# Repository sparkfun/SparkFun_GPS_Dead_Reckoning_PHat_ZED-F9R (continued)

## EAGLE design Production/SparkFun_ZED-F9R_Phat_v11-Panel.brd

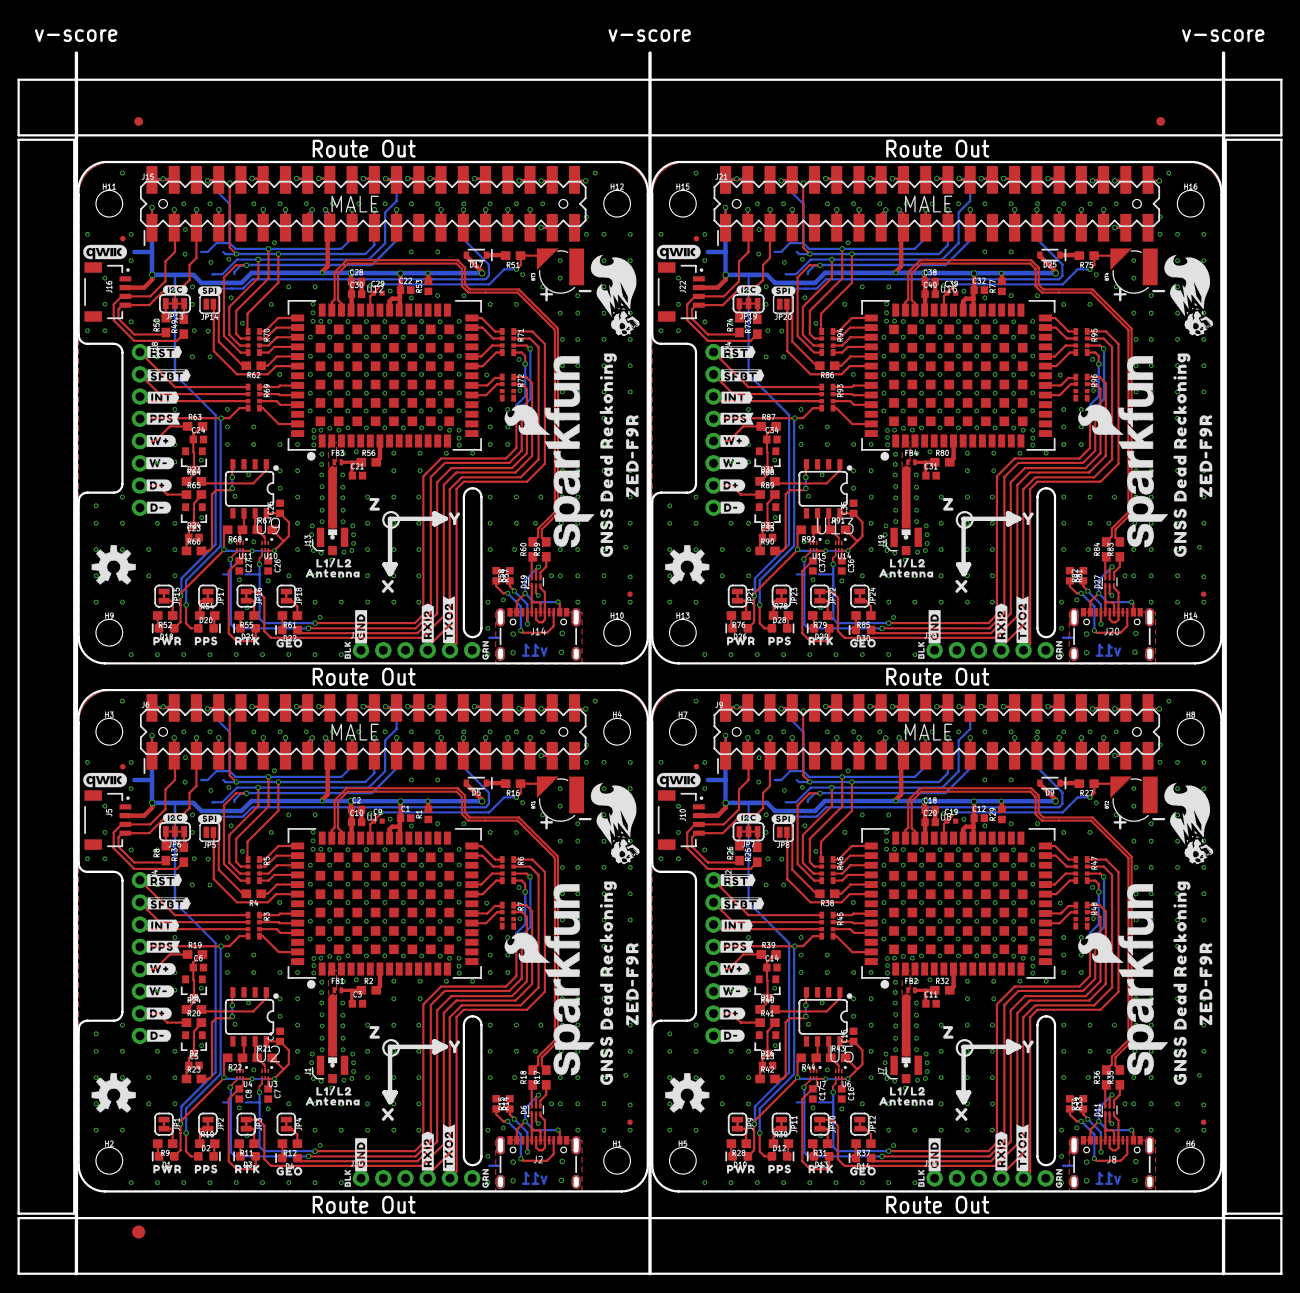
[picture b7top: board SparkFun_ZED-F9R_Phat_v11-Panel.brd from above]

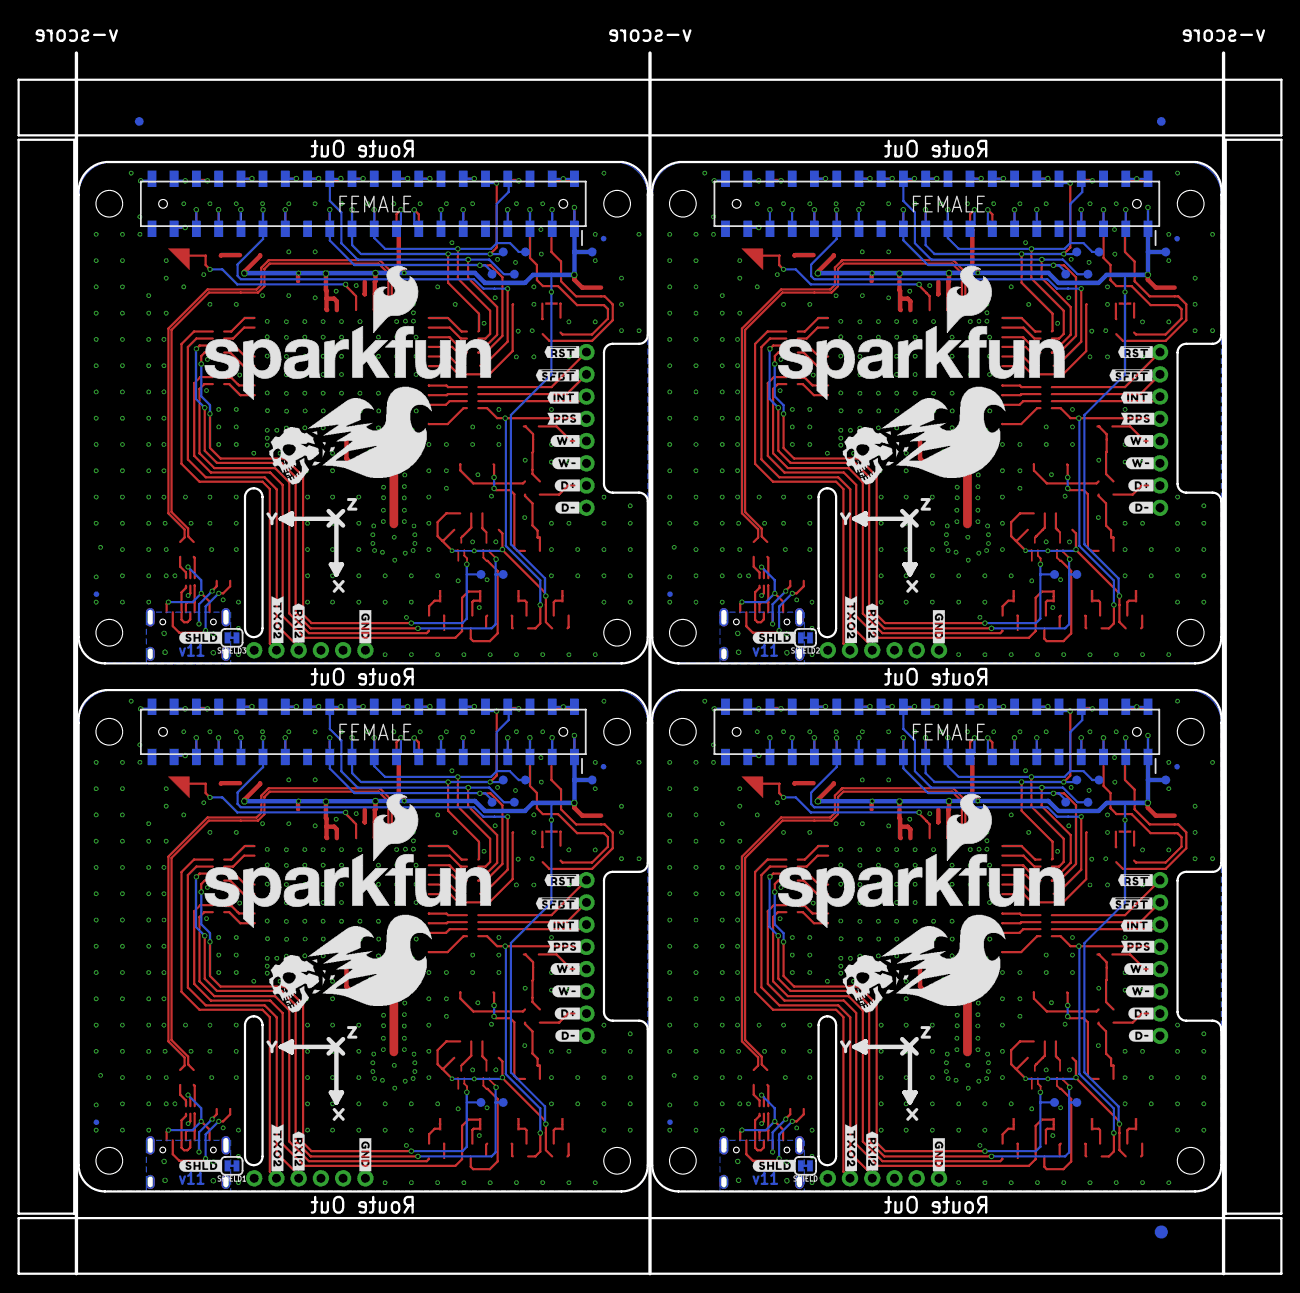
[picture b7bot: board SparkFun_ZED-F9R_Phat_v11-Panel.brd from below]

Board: 2 copper layers, 144.2 x 139.4 mm, 498 parts (111 on the bottom side), 352 nets.

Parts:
BT1, BT2, BT3, BT4: RELOWABLE_BATTERY_MS421R; MS421R_IV03E
C1, C2, C10, C12, C18, C20, C22, C28, C30, C32, C38, C40: 1.0uF; 0402
C3, C11, C21, C31: 47pF; 0402
C4, C7, C8, C15, C16, C17, C25, C26, C27, C35, C36, C37: 0.1uF; 0402
C5, C6, C13, C14, C23, C24, C33, C34: 1nF; 0402
C9, C19, C29, C39: 2.2uF; 0402-TIGHT
D1, D10, D18, D26: RED; LED-0603
D2, D3, D4, D12, D13, D14, D20, D21, D22, D28, D29, D30: BLUE; LED-0603
D5, D9, D17, D25: 0.5A/40V/420mV; SOD-323
D6, D11, D19, D27: PRTR5V0U2F; SOT886
D7, D8, D15, D16, D23, D24, D31, D32: 15V; SOT23-3
E$1, E$2, E$3, E$4: FIDUCIAL-1X2
E$5, E$6: FIDUCIAL-1.5X3
FB1, FB2, FB3, FB4: 120NH; 0402_MURATA
FD1, FD2, FD3, FD4, FD5, FD6, FD7, FD8, FD9, FD10, FD11, FD12, FD13, FD14, FD15, FD16: FIDUCIALUFIDUCIAL; FIDUCIAL-MICRO
H1, H2, H3, H4, H5, H6, H7, H8, H9, H10, H11, H12, H13, H14, H15, H16: STAND-OFFTIGHT; STAND-OFF-TIGHT
J1, J7, J13, J19: U.FL
J2, J8, J14, J20: USB-C-16P-2LAYER-PADS
J3, J11, J17, J23: 1X06_NO_SILK
J4, J12, J18, J24: 1X08_NO_SILK
J5, J10, J16, J22: QWIIC_RIGHT_ANGLE; JST04_1MM_RA
J6, J9, J15, J21: RASPBERRYPI-40-PIN-GPIO_SMD_STACK_NOHOLES_NOREF; RASPBERRY_PI_HAT_40_PIN_SMD_STACKABLE_NOHOLES_NOREF
JP1, JP2, JP3, JP4, JP9, JP10, JP11, JP12, JP15, JP16, JP17, JP18, JP21, JP22, JP23, JP24: JUMPER-SMT_2_NC_TRACE_SILK; SMT-JUMPER_2_NC_TRACE_SILK
JP5, JP8, JP14, JP20: JUMPER-SMT_2_NO_SILK; SMT-JUMPER_2_NO_SILK
JP6, JP7, JP13, JP19: JUMPER-SMT_3_2-NC_TRACE_SILK; SMT-JUMPER_3_2-NC_TRACE_SILK
LOGO1, LOGO6, LOGO9, LOGO12: QWIIC_LOGO_5MM; QWIIC_5MM
LOGO2, LOGO5, LOGO8, LOGO11: OSHW-LOGOM; OSHW-LOGO-M
LOGO3, LOGO4, LOGO7, LOGO10: SFE_LOGO_NAME_FLAME.2_INCH; SFE_LOGO_NAME_FLAME_.2
R1, R29, R53, R77: 100K; 0402
R2, R4, R32, R38, R56, R62, R80, R86: 33; 0603
R3, R5, R6, R7, R45, R46, R47, R48, R69, R70, R71, R72, R93, R94, R95, R96: 33; 1206_RA
R8, R10, R11, R12, R13, R25, R26, R30, R31, R37, R49, R50, R54, R55, R61, R73, R74, R78, R79, R85: 2.2k; 0603
R9, R28, R52, R76: 1k; 0603
R14, R15, R33, R34, R57, R58, R81, R82: 5.1k; 0402
R16, R19, R20, R27, R39, R41, R51, R63, R65, R75, R87, R89: 3.3k; 0603
R17, R18, R35, R36, R59, R60, R83, R84: 27; 0603
R21, R22, R43, R44, R67, R68, R91, R92: 910; 0603
R23, R24, R40, R42, R64, R66, R88, R90: 470; 0603
SHIELD, SHIELD1, SHIELD2, SHIELD3: JUMPER-SMT_2_NC_TRACE_SILK; SMT-JUMPER_2_NC_TRACE_SILK
TP1, TP2, TP3, TP4, TP5, TP6, TP7, TP8, TP9, TP10, TP11, TP12, TP13, TP14, TP15, TP16, TP17, TP18, TP19, TP20, TP21, TP22, TP23, TP24, TP25, TP26, TP27, TP28: TEST-POINT3X4; PAD.03X.04
U1, U8, U12, U16: U-BLOX_ZED-F9R; UBLOX_ZED_F9R
U2, U5, U9, U13: DUAL-OPTO_HCPL-073LSOIC-8; SO08
U3, U4, U6, U7, U10, U11, U14, U15: UHS_INVERTER_SCHMITT_TRIGGER_MPAK2; SIP6_MICROPAK2
U$1, U$48, U$92, U$136: ##RST##28
U$2, U$49, U$93, U$137: ##SFBT##30
U$3, U$59, U$103, U$147: PPS9
U$4, U$58, U$102, U$146: PWR7
U$5, U$61, U$105, U$149: GEO11
U$6, U$66, U$110, U$154: #RXI2#34
U$7, U$50, U$94, U$138: #INT#1
U$8, U$51, U$95, U$139: #PPS#3
U$9, U$30, U$89, U$133: SFE_LOGO_NAME_FLAME_.3@1
U$10, U$67, U$111, U$155: #TXO2#235
U$11, U$52, U$96, U$140: #W##2253
U$12, U$53, U$97, U$141: #W##2254
U$13, U$54, U$98, U$142: #D##2249
U$14, U$77, U$121, U$165: GNSS_DEAD_RECKONING25
U$15, U$55, U$99, U$143: #D##2250
U$16, U$68, U$112, U$156: ZED#F9R25
U$17, U$62, U$106, U$150: BLK22
U$18, U$19, U$64, U$65, U$108, U$109, U$152, U$153: #GND#20
U$20, U$56, U$100, U$144: #SPI#4
U$21, U$78, U$122, U$166: L1#L26
U$22, U$57, U$101, U$145: #I2C#5
U$23, U$60, U$104, U$148: RTK13
U$24, U$63, U$107, U$151: GRN23
U$25, U$28, U$85, U$86, U$129, U$130, U$173, U$174: Z20
U$26, U$29, U$87, U$88, U$131, U$132, U$175, U$176: Y19
U$27, U$45, U$83, U$84, U$127, U$128, U$171, U$172: X18
U$31, U$36, U$46, U$47, U$90, U$91, U$134, U$135: DEAD#RECKONING#GPS#BOARD#SILK#FINAL#JPG
U$32, U$69, U$113, U$157: ##RST##27
U$33, U$70, U$114, U$158: ##SFBT##29
U$34, U$71, U$115, U$159: #INT#0
U$35, U$72, U$116, U$160: #PPS#2
U$37, U$73, U$117, U$161: #W##2251
U$38, U$74, U$118, U$162: #W##2252
U$39, U$75, U$119, U$163: #D##2247
U$40, U$76, U$120, U$164: #D##2248
U$41, U$79, U$123, U$167: ANTENNA6
U$42, U$80, U$124, U$168: #TXO2#236
U$43, U$81, U$125, U$169: #RXI2#35
U$44, U$82, U$126, U$170: #SHLD#2258

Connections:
3.3V: C1.1, C2.1, C4.1, C7.1, C8.1, C10.1, D1.A, D3.A, D5.A, J5.2, J6.1, J6.1B, J6.17, J6.17B, JP6.2, R1.2, R21.2, R22.2, TP5.P$1, U1.P33, U1.P34, U1.P38, U2.8, U3.P6, U4.P6
3.3V1: C12.1, C15.1, C16.1, C17.1, C18.1, C20.1, D9.A, D10.A, D13.A, J9.1, J9.1B, J9.17, J9.17B, J10.2, JP7.2, R29.2, R43.2, R44.2, TP12.P$1, U5.8, U6.P6, U7.P6, U8.P33, U8.P34, U8.P38
3.3V2: C22.1, C25.1, C26.1, C27.1, C28.1, C30.1, D17.A, D18.A, D21.A, J15.1, J15.1B, J15.17, J15.17B, J16.2, JP13.2, R53.2, R67.2, R68.2, TP19.P$1, U9.8, U10.P6, U11.P6, U12.P33, U12.P34, U12.P38
3.3V3: C32.1, C35.1, C36.1, C37.1, C38.1, C40.1, D25.A, D26.A, D29.A, J21.1, J21.1B, J21.17, J21.17B, J22.2, JP19.2, R77.2, R91.2, R92.2, TP26.P$1, U13.8, U14.P6, U15.P6, U16.P33, U16.P34, U16.P38
5V: J6.2, J6.2B, J6.4, J6.4B
5V1: J9.2, J9.2B, J9.4, J9.4B
5V2: J15.2, J15.2B, J15.4, J15.4B
5V3: J21.2, J21.2B, J21.4, J21.4B
!RESET: J4.1, R3.P1
!RESET1: J12.1, R45.P1
!RESET2: J18.1, R69.P1
!RESET3: J24.1, R93.P1
!SAFEBOOT: J4.2, R3.P2
!SAFEBOOT1: J12.2, R45.P2
!SAFEBOOT2: J18.2, R69.P2
!SAFEBOOT3: J24.2, R93.P2
CE1: J6.26, J6.26B
CE2: J9.26, J9.26B
CE3: J15.26, J15.26B
CE4: J21.26, J21.26B
DIR+: J4.7, R20.1
DIR+1: J12.7, R41.1
DIR+2: J18.7, R65.1
DIR+3: J24.7, R89.1
DIR_IN: R23.2, U2.4
DIR_IN1: R42.2, U5.4
DIR_IN2: R66.2, U9.4
DIR_IN3: R90.2, U13.4
DIR_OUT: R6.P6, TP7.P$1, U4.P4
DIR_OUT1: R47.P6, TP14.P$1, U7.P4
DIR_OUT2: R71.P6, TP21.P$1, U11.P4
DIR_OUT3: R95.P6, TP28.P$1, U15.P4
DIR_SCHMITT: R22.1, U2.6, U4.P2
DIR_SCHMITT1: R44.1, U5.6, U7.P2
DIR_SCHMITT2: R68.1, U9.6, U11.P2
DIR_SCHMITT3: R92.1, U13.6, U15.P2
DMINUS: R18.2, U1.P39
DMINUS1: R36.2, U8.P39
DMINUS2: R60.2, U12.P39
DMINUS3: R84.2, U16.P39
DPLUS: R17.2, U1.P40
DPLUS1: R35.2, U8.P40
DPLUS2: R59.2, U12.P40
DPLUS3: R83.2, U16.P40
D_SEL: JP5.1, U1.P47
D_SEL1: JP8.1, U8.P47
D_SEL2: JP14.1, U12.P47
D_SEL3: JP20.1, U16.P47
GEOF_STAT: D4.A, R7.P7
GEOF_STAT1: D14.A, R48.P7
GEOF_STAT2: D22.A, R72.P7
GEOF_STAT3: D30.A, R96.P7
GND: BT1.-, C1.2, C2.2, C3.2, C4.2, C5.2, C6.2, C7.2, C8.2, C9.2, C10.2, D6.2, D7.1, D8.1, J1.1, J1.2, J2.GND, J2.GND2, J3.1, J4.6, J4.8, J5.1, J6.6, J6.6B, J6.9, J6.9B, J6.14, J6.14B, J6.20, J6.20B, J6.25, J6.25B, J6.30, J6.30B, J6.34, J6.34B, J6.39, J6.39B, JP1.1, JP2.1, JP4.1, JP5.2, R1.1, R14.1, R15.1, SHIELD.1, U1.G1, U1.G2, U1.G3, U1.G4, U1.G5, U1.G6, U1.G7, U1.G8, U1.G9, U1.G10, U1.G11, U1.G12, U1.G13, U1.G14, U1.G15, U1.G16, U1.G17, U1.G18, U1.G19, U1.G20, U1.G21, U1.G22, U1.G23, U1.G24, U1.G25, U1.G26, U1.G27, U1.G28, U1.G29, U1.G30, U1.G31, U1.G32, U1.G33, U1.G34, U1.G35, U1.G36, U1.G37, U1.G38, U1.G39, U1.G40, U1.G41, U1.G42, U1.G43, U1.G44, U1.G45, U1.G46, U1.G47, U1.G48, U1.P1, U1.P3, U1.P12, U1.P14, U1.P32, U1.P37, U1.P41, U1.P48, U2.2, U2.3, U2.5, U3.P3, U4.P3
GND1: BT2.-, C11.2, C12.2, C13.2, C14.2, C15.2, C16.2, C17.2, C18.2, C19.2, C20.2, D11.2, D15.1, D16.1, J7.1, J7.2, J8.GND, J8.GND2, J9.6, J9.6B, J9.9, J9.9B, J9.14, J9.14B, J9.20, J9.20B, J9.25, J9.25B, J9.30, J9.30B, J9.34, J9.34B, J9.39, J9.39B, J10.1, J11.1, J12.6, J12.8, JP8.2, JP9.1, JP11.1, JP12.1, R29.1, R33.1, R34.1, SHIELD1.1, U5.2, U5.3, U5.5, U6.P3, U7.P3, U8.G1, U8.G2, U8.G3, U8.G4, U8.G5, U8.G6, U8.G7, U8.G8, U8.G9, U8.G10, U8.G11, U8.G12, U8.G13, U8.G14, U8.G15, U8.G16, U8.G17, U8.G18, U8.G19, U8.G20, U8.G21, U8.G22, U8.G23, U8.G24, U8.G25, U8.G26, U8.G27, U8.G28, U8.G29, U8.G30, U8.G31, U8.G32, U8.G33, U8.G34, U8.G35, U8.G36, U8.G37, U8.G38, U8.G39, U8.G40, U8.G41, U8.G42, U8.G43, U8.G44, U8.G45, U8.G46, U8.G47, U8.G48, U8.P1, U8.P3, U8.P12, U8.P14, U8.P32, U8.P37, U8.P41, U8.P48
GND2: BT3.-, C21.2, C22.2, C23.2, C24.2, C25.2, C26.2, C27.2, C28.2, C29.2, C30.2, D19.2, D23.1, D24.1, J13.1, J13.2, J14.GND, J14.GND2, J15.6, J15.6B, J15.9, J15.9B, J15.14, J15.14B, J15.20, J15.20B, J15.25, J15.25B, J15.30, J15.30B, J15.34, J15.34B, J15.39, J15.39B, J16.1, J17.1, J18.6, J18.8, JP14.2, JP15.1, JP17.1, JP18.1, R53.1, R57.1, R58.1, SHIELD2.1, U9.2, U9.3, U9.5, U10.P3, U11.P3, U12.G1, U12.G2, U12.G3, U12.G4, U12.G5, U12.G6, U12.G7, U12.G8, U12.G9, U12.G10, U12.G11, U12.G12, U12.G13, U12.G14, U12.G15, U12.G16, U12.G17, U12.G18, U12.G19, U12.G20, U12.G21, U12.G22, U12.G23, U12.G24, U12.G25, U12.G26, U12.G27, U12.G28, U12.G29, U12.G30, U12.G31, U12.G32, U12.G33, U12.G34, U12.G35, U12.G36, U12.G37, U12.G38, U12.G39, U12.G40, U12.G41, U12.G42, U12.G43, U12.G44, U12.G45, U12.G46, U12.G47, U12.G48, U12.P1, U12.P3, U12.P12, U12.P14, U12.P32, U12.P37, U12.P41, U12.P48
GND3: BT4.-, C31.2, C32.2, C33.2, C34.2, C35.2, C36.2, C37.2, C38.2, C39.2, C40.2, D27.2, D31.1, D32.1, J19.1, J19.2, J20.GND, J20.GND2, J21.6, J21.6B, J21.9, J21.9B, J21.14, J21.14B, J21.20, J21.20B, J21.25, J21.25B, J21.30, J21.30B, J21.34, J21.34B, J21.39, J21.39B, J22.1, J23.1, J24.6, J24.8, JP20.2, JP21.1, JP23.1, JP24.1, R77.1, R81.1, R82.1, SHIELD3.1, U13.2, U13.3, U13.5, U14.P3, U15.P3, U16.G1, U16.G2, U16.G3, U16.G4, U16.G5, U16.G6, U16.G7, U16.G8, U16.G9, U16.G10, U16.G11, U16.G12, U16.G13, U16.G14, U16.G15, U16.G16, U16.G17, U16.G18, U16.G19, U16.G20, U16.G21, U16.G22, U16.G23, U16.G24, U16.G25, U16.G26, U16.G27, U16.G28, U16.G29, U16.G30, U16.G31, U16.G32, U16.G33, U16.G34, U16.G35, U16.G36, U16.G37, U16.G38, U16.G39, U16.G40, U16.G41, U16.G42, U16.G43, U16.G44, U16.G45, U16.G46, U16.G47, U16.G48, U16.P1, U16.P3, U16.P12, U16.P14, U16.P32, U16.P37, U16.P41, U16.P48
GP1: J9.31, J9.31B
GP2: J9.32, J9.32B
GP3: J9.33, J9.33B
GP4: J6.7, J6.7B
GP5: J9.36, J9.36B
GP6: J6.31, J6.31B
GP7: J9.35, J9.35B
GP8: J9.38, J9.38B
GP9: J9.40, J9.40B
GP10: J9.37, J9.37B
GP11: J9.7, J9.7B
GP12: J6.32, J6.32B
GP13: J6.33, J6.33B
GP14: J9.11, J9.11B
GP15: J9.12, J9.12B
GP16: J6.36, J6.36B
GP17: J6.11, J6.11B
GP18: J6.12, J6.12B
GP19: J6.35, J6.35B
GP20: J6.38, J6.38B
GP21: J6.40, J6.40B
GP22: J6.15, J6.15B
GP23: J6.16, J6.16B
GP24: J6.18, J6.18B
GP25: J6.22, J6.22B
GP26: J6.37, J6.37B
GP27: J6.13, J6.13B
GP28: J9.15, J9.15B
GP29: J9.16, J9.16B
GP30: J9.18, J9.18B
GP31: J9.22, J9.22B
GP32: J9.13, J9.13B
GP33: J15.31, J15.31B
GP34: J15.32, J15.32B
GP35: J15.33, J15.33B
GP36: J15.36, J15.36B
GP37: J15.35, J15.35B
GP38: J15.38, J15.38B
GP39: J15.40, J15.40B
GP40: J15.37, J15.37B
GP41: J15.7, J15.7B
GP42: J15.11, J15.11B
GP43: J15.12, J15.12B
GP44: J15.15, J15.15B
GP45: J15.16, J15.16B
GP46: J15.18, J15.18B
GP47: J15.22, J15.22B
GP48: J15.13, J15.13B
GP49: J21.31, J21.31B
GP50: J21.32, J21.32B
GP51: J21.33, J21.33B
GP52: J21.36, J21.36B
GP53: J21.35, J21.35B
GP54: J21.38, J21.38B
GP55: J21.40, J21.40B
GP56: J21.37, J21.37B
GP57: J21.7, J21.7B
GP58: J21.11, J21.11B
GP59: J21.12, J21.12B
GP60: J21.15, J21.15B
GP61: J21.16, J21.16B
GP62: J21.18, J21.18B
GP63: J21.22, J21.22B
GP64: J21.13, J21.13B
ID_SC: J6.28, J6.28B
ID_SC1: J9.28, J9.28B
ID_SC2: J15.28, J15.28B
ID_SC3: J21.28, J21.28B
ID_SD: J6.27, J6.27B
ID_SD1: J9.27, J9.27B
ID_SD2: J15.27, J15.27B
ID_SD3: J21.27, J21.27B
INT: J4.3, R3.P3
INT1: J12.3, R45.P3
INT2: J18.3, R69.P3
INT3: J24.3, R93.P3
unnamed: JP6.1, R13.2
unnamed: D5.C, R16.2
unnamed: JP6.3, R8.2
unnamed: D1.C, R9.2
unnamed: C3.1, FB1.P2, R2.1
unnamed: D6.6, R18.1
unnamed: D6.4, R17.1
unnamed: JP1.2, R9.1
unnamed: D6.3, J2.A6, J2.B6
unnamed: D6.5, J2.VBUS1, J2.VBUS2
unnamed: D6.1, J2.A7, J2.B7
unnamed: J2.B5, R14.2
unnamed: R3.P8, U1.P49
unnamed: R3.P6, U1.P51
unnamed: R5.P6, U1.P44
unnamed: JP4.2, R12.1
unnamed: D4.C, R12.2
unnamed: J2.A5, R15.2
unnamed: R5.P5, U1.P45
unnamed: R4.1, U1.P46
unnamed: R5.P8, U1.P42
unnamed: JP3.2, R11.1
unnamed: JP2.2, R10.1
unnamed: D2.C, R10.2
unnamed: D3.C, R11.2
unnamed: R5.P7, U1.P43
unnamed: C6.1, D8.3, R19.2, R24.1
unnamed: R7.P2, U1.P19
unnamed: R7.P1, U1.P20
unnamed: R3.P5, U1.P53
unnamed: R3.P7, U1.P50
unnamed: R6.P1, U1.P27
unnamed: R6.P2, U1.P26
unnamed: R6.P4, U1.P22
unnamed: R6.P3, U1.P23
unnamed: C5.1, D7.3, R20.2, R23.1
unnamed: D9.C, R27.2
unnamed: JP7.1, R25.2
unnamed: JP7.3, R26.2
unnamed: JP10.2, R31.1
unnamed: JP11.2, R30.1
unnamed: D12.C, R30.2
unnamed: D13.C, R31.2
unnamed: D10.C, R28.2
unnamed: JP9.2, R28.1
unnamed: C11.1, FB2.P2, R32.1
unnamed: J8.B5, R33.2
unnamed: J8.A5, R34.2
unnamed: D11.5, J8.VBUS1, J8.VBUS2
unnamed: D11.3, J8.A6, J8.B6
unnamed: D11.1, J8.A7, J8.B7
unnamed: D11.6, R36.1
unnamed: D11.4, R35.1
unnamed: JP12.2, R37.1
unnamed: D14.C, R37.2
unnamed: R45.P8, U8.P49
unnamed: R45.P6, U8.P51
unnamed: R46.P6, U8.P44
unnamed: R46.P5, U8.P45
unnamed: R38.1, U8.P46
unnamed: R46.P8, U8.P42
unnamed: R46.P7, U8.P43
unnamed: R48.P2, U8.P19
unnamed: R48.P1, U8.P20
unnamed: R45.P5, U8.P53
unnamed: R45.P7, U8.P50
unnamed: R47.P1, U8.P27
unnamed: R47.P2, U8.P26
unnamed: R47.P4, U8.P22
unnamed: R47.P3, U8.P23
unnamed: C14.1, D15.3, R39.2, R40.1
unnamed: C13.1, D16.3, R41.2, R42.1
unnamed: D17.C, R51.2
unnamed: JP13.1, R49.2
unnamed: JP13.3, R50.2
unnamed: JP16.2, R55.1
unnamed: JP17.2, R54.1
unnamed: D20.C, R54.2
unnamed: D21.C, R55.2
unnamed: D18.C, R52.2
unnamed: JP15.2, R52.1
unnamed: C21.1, FB3.P2, R56.1
unnamed: J14.B5, R57.2
unnamed: J14.A5, R58.2
unnamed: D19.5, J14.VBUS1, J14.VBUS2
unnamed: D19.3, J14.A6, J14.B6
unnamed: D19.1, J14.A7, J14.B7
unnamed: D19.6, R60.1
unnamed: D19.4, R59.1
unnamed: JP18.2, R61.1
unnamed: D22.C, R61.2
unnamed: R69.P8, U12.P49
unnamed: R69.P6, U12.P51
unnamed: R70.P6, U12.P44
unnamed: R70.P5, U12.P45
unnamed: R62.1, U12.P46
unnamed: R70.P8, U12.P42
unnamed: R70.P7, U12.P43
unnamed: R72.P2, U12.P19
unnamed: R72.P1, U12.P20
unnamed: R69.P5, U12.P53
unnamed: R69.P7, U12.P50
unnamed: R71.P1, U12.P27
unnamed: R71.P2, U12.P26
unnamed: R71.P4, U12.P22
unnamed: R71.P3, U12.P23
unnamed: C24.1, D23.3, R63.2, R64.1
unnamed: C23.1, D24.3, R65.2, R66.1
unnamed: D25.C, R75.2
unnamed: JP19.1, R73.2
unnamed: JP19.3, R74.2
unnamed: JP22.2, R79.1
unnamed: JP23.2, R78.1
unnamed: D28.C, R78.2
unnamed: D29.C, R79.2
unnamed: D26.C, R76.2
unnamed: JP21.2, R76.1
unnamed: C31.1, FB4.P2, R80.1
unnamed: J20.B5, R81.2
unnamed: J20.A5, R82.2
unnamed: D27.5, J20.VBUS1, J20.VBUS2
unnamed: D27.3, J20.A6, J20.B6
unnamed: D27.1, J20.A7, J20.B7
unnamed: D27.6, R84.1
unnamed: D27.4, R83.1
unnamed: JP24.2, R85.1
unnamed: D30.C, R85.2
unnamed: R93.P8, U16.P49
unnamed: R93.P6, U16.P51
unnamed: R94.P6, U16.P44
unnamed: R94.P5, U16.P45
unnamed: R86.1, U16.P46
unnamed: R94.P8, U16.P42
unnamed: R94.P7, U16.P43
unnamed: R96.P2, U16.P19
unnamed: R96.P1, U16.P20
unnamed: R93.P5, U16.P53
unnamed: R93.P7, U16.P50
unnamed: R95.P1, U16.P27
unnamed: R95.P2, U16.P26
unnamed: R95.P4, U16.P22
unnamed: R95.P3, U16.P23
unnamed: C34.1, D31.3, R87.2, R88.1
unnamed: C33.1, D32.3, R89.2, R90.1
PPS: D2.A, J4.4, R3.P4
PPS1: D12.A, J12.4, R45.P4
PPS2: D20.A, J18.4, R69.P4
PPS3: D28.A, J24.4, R93.P4
QWIIC_SCL: J5.4, J6.5, J6.5B, R8.1
QWIIC_SCL1: J9.5, J9.5B, J10.4, R26.1
QWIIC_SCL2: J15.5, J15.5B, J16.4, R50.1
QWIIC_SCL3: J21.5, J21.5B, J22.4, R74.1
QWIIC_SDA: J5.3, J6.3, J6.3B, R13.1
QWIIC_SDA1: J9.3, J9.3B, J10.3, R25.1
QWIIC_SDA2: J15.3, J15.3B, J16.3, R49.1
QWIIC_SDA3: J21.3, J21.3B, J22.3, R73.1
RF_IN: FB1.P1, J1.FEED, U1.P2
RF_IN1: FB2.P1, J7.FEED, U8.P2
RF_IN2: FB3.P1, J13.FEED, U12.P2
RF_IN3: FB4.P1, J19.FEED, U16.P2
RTK_STAT: JP3.1, R7.P8
RTK_STAT1: JP10.1, R48.P8
RTK_STAT2: JP16.1, R72.P8
RTK_STAT3: JP22.1, R96.P8
RXI1: J11.4, R47.P7
RXI2: J3.4, R6.P7
RXI3: J17.4, R71.P7
RXI4: J23.4, R95.P7
RXI/CIPO: J6.8, J6.8B, J6.19, J6.19B, R5.P2, TP1.P$1
RXI/CIPO1: J9.8, J9.8B, J9.19, J9.19B, R46.P2, TP8.P$1
RXI/CIPO2: J15.8, J15.8B, J15.19, J15.19B, R70.P2, TP15.P$1
RXI/CIPO3: J21.8, J21.8B, J21.19, J21.19B, R94.P2, TP22.P$1
SCL/CLK: J6.23, J6.23B, R5.P4, TP3.P$1
SCL/CLK1: J9.23, J9.23B, R46.P4, TP10.P$1
SCL/CLK2: J15.23, J15.23B, R70.P4, TP17.P$1
SCL/CLK3: J21.23, J21.23B, R94.P4, TP24.P$1
SDA/!CS: J6.24, J6.24B, R5.P3, TP4.P$1
SDA/!CS1: J9.24, J9.24B, R46.P3, TP11.P$1
SDA/!CS2: J15.24, J15.24B, R70.P3, TP18.P$1
SDA/!CS3: J21.24, J21.24B, R94.P3, TP25.P$1
SHIELD: J2.SHLD1, J2.SHLD2, J2.SHLD3, J2.SHLD4, SHIELD.2
SHIELD1: J8.SHLD1, J8.SHLD2, J8.SHLD3, J8.SHLD4, SHIELD1.2
SHIELD2: J14.SHLD1, J14.SHLD2, J14.SHLD3, J14.SHLD4, SHIELD2.2
SHIELD3: J20.SHLD1, J20.SHLD2, J20.SHLD3, J20.SHLD4, SHIELD3.2
TXO1: J11.5, R47.P8
TXO2: J3.5, R6.P8
TXO3: J17.5, R71.P8
TXO4: J23.5, R95.P8
TXO/COPI: J6.10, J6.10B, J6.21, J6.21B, R5.P1, TP2.P$1
TXO/COPI1: J9.10, J9.10B, J9.21, J9.21B, R46.P1, TP9.P$1
TXO/COPI2: J15.10, J15.10B, J15.21, J15.21B, R70.P1, TP16.P$1
TXO/COPI3: J21.10, J21.10B, J21.21, J21.21B, R94.P1, TP23.P$1
TX_READY: J6.29, J6.29B, R4.2
TX_READY1: J9.29, J9.29B, R38.2
TX_READY2: J15.29, J15.29B, R62.2
TX_READY3: J21.29, J21.29B, R86.2
V_BATT: BT1.+, C9.1, R16.1, U1.P36
V_BATT1: BT2.+, C19.1, R27.1, U8.P36
V_BATT2: BT3.+, C29.1, R51.1, U12.P36
V_BATT3: BT4.+, C39.1, R75.1, U16.P36
V_RF: R2.2, U1.P7
V_RF1: R32.2, U8.P7
V_RF2: R56.2, U12.P7
V_RF3: R80.2, U16.P7
WT+: J4.5, R19.1
WT+1: J12.5, R39.1
WT+2: J18.5, R63.1
WT+3: J24.5, R87.1
WT_IN: R24.2, U2.1
WT_IN1: R40.2, U5.1
WT_IN2: R64.2, U9.1
WT_IN3: R88.2, U13.1
WT_OUT: R6.P5, TP6.P$1, U3.P4
WT_OUT1: R47.P5, TP13.P$1, U6.P4
WT_OUT2: R71.P5, TP20.P$1, U10.P4
WT_OUT3: R95.P5, TP27.P$1, U14.P4
WT_SCHMITT: R21.1, U2.7, U3.P2
WT_SCHMITT1: R43.1, U5.7, U6.P2
WT_SCHMITT2: R67.1, U9.7, U10.P2
WT_SCHMITT3: R91.1, U13.7, U14.P2

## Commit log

2019-10-10 Adds basic layout to board and creates (most of) ZED-F9K device
2019-10-10 Finishes ZED-F9K footprint
2019-10-10 Creates device for ZED-F9K (footprint and symbol)
2019-10-10 Adds circuitry for active antenna or RF_IN
2019-10-11 Adds power circuitry with ESD protection, adds LEDs
2019-10-24 Adds I/O protection to INPUTS using new part, removes active antenna circuitry in place of VCC bias for external patch active antennas
    * Localizes parts into a rough shape for final product
2019-10-24 Just some light trace work to get a feel for layout
2020-01-08 Adds micro pi hat layout
2020-01-09 Adds trace work for piHat version - still needs silk
2020-01-20 Replaces micro hat with regular hat
2020-01-20 Renames files to reflect change to pi hat
2020-01-20 Add prelimnary trace routing
2020-01-20 Adds nets for data lines
2020-01-21 Finishes pi hat design and adds some labels
2020-01-22 Solidifies breakout board size
2020-01-24 Finalizes trace work for the Breakout board
2020-01-24 Adds a few more vias
2020-01-27 Updates Modules, adjusts ground pour.
2020-01-27 More work to ground pour
2020-01-27 Fixes a few traces
2020-01-28 Adds labels to breakout board
2020-01-28 Adds labels to pi hat
2020-01-28 Adds labels to the pi-hat
2020-01-29 Fixes labels on BoB
2020-01-31 Moves buzzard labels to their own folder - updates breakout board with better labeling
    * fixes I2C lines being backwards
    * Moves D+ and D- lines around
2020-01-31 Moves buzzard label folder to breakout folder
2020-01-31 Adjust pi-hat design
    * Moves jumpers to teh top
    * moves labels for LEDs to teh Edge
    * Moves USB and FTDI header to the bottom edge
    * Fixes ESD protection IC routing
    * Fixes RX/TX
2020-01-31 Fixes routing for ESD protection IC
2020-02-04 Replaces some 0402 components for 0603 on the pi-hat
2020-02-11 Adds F9R datasheets, updates design with wheel ticks, direction pins, and adds 33 Ohm filtering resistors to all I/O
2020-02-11 Updates breakout board with the same parts as the pi hat
2020-02-12 Touches up some vias and traces
2020-02-13 Gerbers for both boards
2020-02-14 Moves library, adds breakout board - circuit for wheel ticks and direction input
2020-02-14 Adds inverter with schmitt trigger to library
2020-02-14 Deletes uneccessary optoisolator
2020-02-17 Adds the automotive interface breakout board
2020-02-17 Renames wheelDir_BoB To Automotive Interafce BoB
2020-02-17 Updates the optocoupler in the Automotive breakout
2020-02-17 Updates schmitt trigger on Automoative Interface board
2020-02-17 CAMs the Automotive Interface Board, updates parts in library with digikey links
2020-02-25 Changes PTH header to double SMD male/femail combination
2020-02-27 Adds test point for power
2020-03-18 Adds wheel tick and direction circuit to pi-hat
2020-03-18 Routes wheel tick and direction circuitry
2020-03-23 Adds automotive certified diode to wt/dir circuitry
    * Adds wt/dir circuitry to both breakout board and pi hat
2020-03-23 Adds labels for new PTH for wt/dir lines
2020-03-23 Updates designs with new X7R capacitors
2020-03-26 Removes gerbers, removes caps from schmitt trigger on both designs, adds 1uF cap to V_USB on breakout
2020-03-26 Adds 1uF Cap to V_USB line
2020-03-27 Updates wheel tick and direction circuitry with correct grounding
2020-03-27 Removes automotive breakout and breakout board
2020-03-27 Moves files out of "Phat" folder
2020-03-27 Renames files to correct module
2020-03-27 Replaces 9-pin connector with 8-pin
2020-03-27 Renumbers parts, adds PROD_ID for new parts
2020-03-28 Fixe RF trace, fixes silk, moves version number, fixes D+ and D- traces
    * Changes jumper labels in schematic
2020-03-28 Updates silk, fixes RF trace, moves some traces for better clearance, adds wt/dir text to schematic
2020-03-31 Adds 33 Ohm resistor arrays and custom silk
2020-03-31 Updates all parts to parts in the Eagle Library
2020-03-31 Replaces 910 Ohm resistor with part from Eagle Library
2020-03-31 Updates cooool skull silk
2020-03-31 Adds Panel, removes buzzard labels
2020-03-31 Fixes issue with panel
2020-03-31 Adds silk for 3 axes and repanelizes
2020-04-03 Replaces 6.3V rated 0.1uF caps with 10V rated ones
2020-04-03 Replaces one of the .1uF with a 1uF Capacitor
2020-06-12 Add file names in .gitignore to ignore
2021-01-08 Adding u-blox Documents
2022-08-18 Updates silk, updates schmitt trigger package and symbol
    * Updates schematic layout
2022-08-29 Updates F9R module, Fixes various trace overlaps and acid traps
    * Updates resistor values on LEDs
    * Adds more capacitance to power lines
2022-08-30 Removes old design files
2022-08-30 Renames design files
2022-08-30 Adds new production files
2023-04-24 Update ZED-F9R Datasheet
    Adding latest ZED-F9R datasheet release (April, 2023).
2023-04-24 Delete ZED-F9R_Datasheet_(UBX-19054459)
    Removing old ZED-F9R datasheet that was replaced with the latest release (April, 2023).
2023-06-13 Update u-blox Integration Manual and Interface Descriptions for ZED-F9R-01B
